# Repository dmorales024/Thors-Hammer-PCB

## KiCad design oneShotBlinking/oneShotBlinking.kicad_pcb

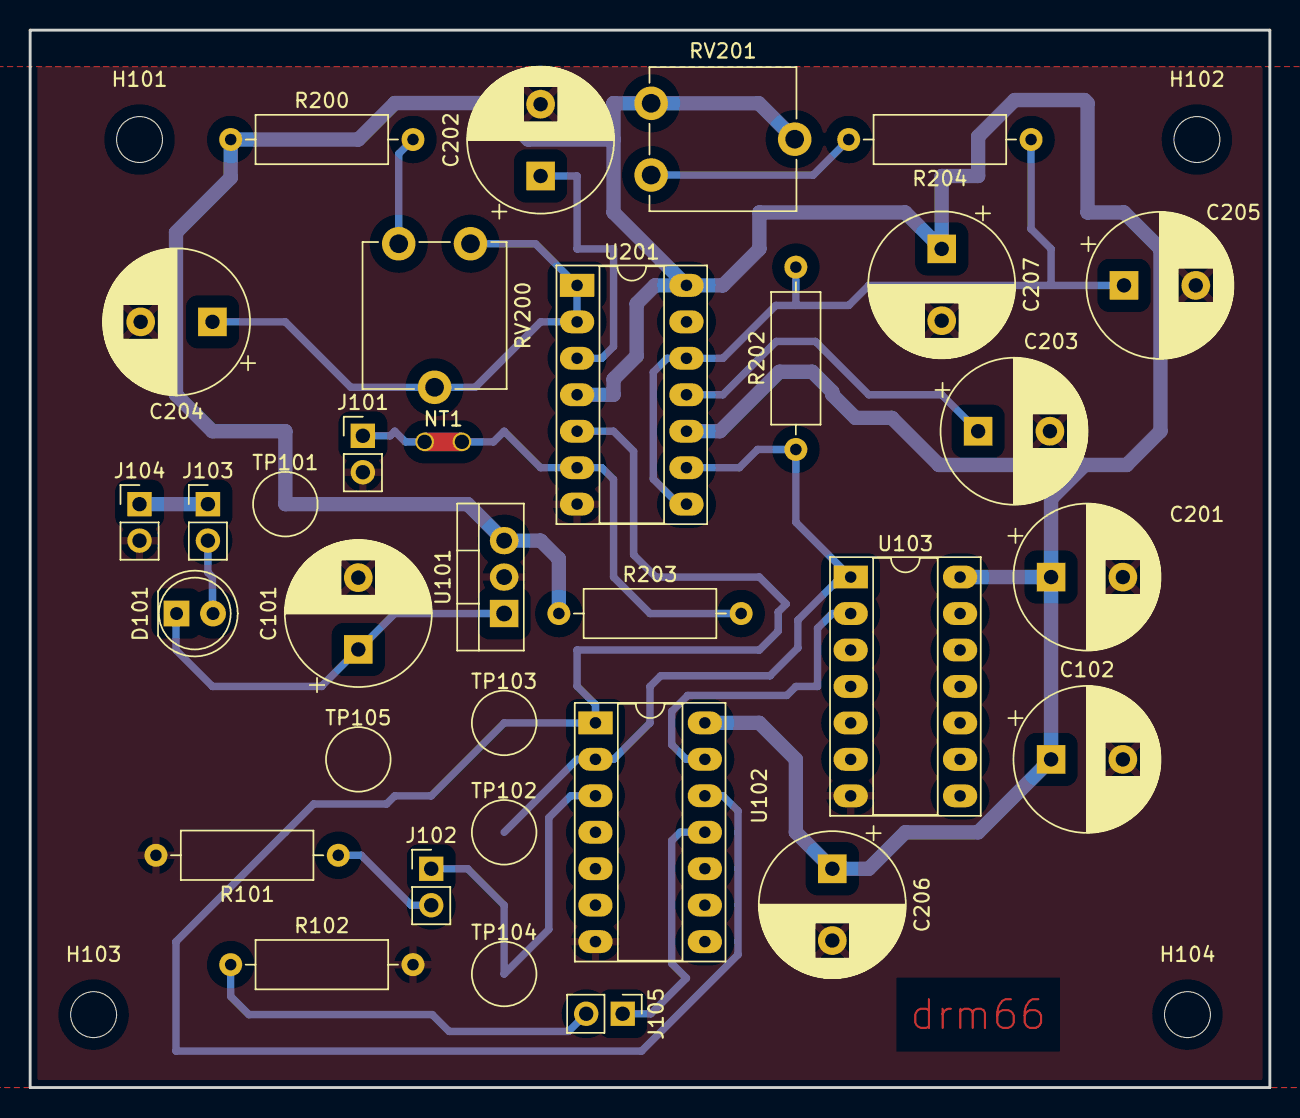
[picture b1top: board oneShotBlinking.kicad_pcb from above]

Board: 2 copper layers, 86.4 x 73.7 mm, 37 parts (0 on the bottom side), 20 nets.

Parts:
C101, C102, C204: 10u; CP_Radial_D10.0mm_P5.00mm
C201, C206, C207: 100n; CP_Radial_D10.0mm_P5.00mm
C202, C203: 0.01u; CP_Radial_D10.0mm_P5.00mm
C205: 1u; CP_Radial_D10.0mm_P5.00mm
D101: RevPol_PwrStatus; LED_D5.0mm
H101, H102, H103, H104: MountingHole; MountingHole_3.2mm_M3
J101: Push Button; PinHeader_1x02_P2.54mm_Vertical
J102, J105: LED; PinHeader_1x02_P2.54mm_Vertical
J103: Power Switch; PinHeader_1x02_P2.54mm_Vertical
J104: BATT; PinHeader_1x02_P2.54mm_Vertical
NT1: To_Button; NetTie-2_THT_Pad1.0mm
R101, R102: 1k; R_Axial_DIN0309_L9.0mm_D3.2mm_P12.70mm_Horizontal
R200: 455k; R_Axial_DIN0309_L9.0mm_D3.2mm_P12.70mm_Horizontal
R202: 42.2k; R_Axial_DIN0309_L9.0mm_D3.2mm_P12.70mm_Horizontal
R203: 10k; R_Axial_DIN0309_L9.0mm_D3.2mm_P12.70mm_Horizontal
R204: 100k; R_Axial_DIN0309_L9.0mm_D3.2mm_P12.70mm_Horizontal
RV200, RV201: 0-100k; Potentiometer_ACP_CA9-V10_Vertical
TP101: VCC; TestPoint_Pad_D4.0mm
TP102: AstableOut; TestPoint_Pad_D4.0mm
TP103: MonoOut; TestPoint_Pad_D4.0mm
TP104: LightOut; TestPoint_Pad_D4.0mm
TP105: GND; TestPoint_Pad_D4.0mm
U101: LM7805_TO220; TO-220-3_Vertical
U102: 4081; DIP-14_W7.62mm_Socket_LongPads
U103: 74LS04; DIP-14_W7.62mm_Socket_LongPads
U201: LM556; DIP-14_W7.62mm_Socket_LongPads

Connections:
+6V: J103.1, J104.1
/Button_Press: J101.1, NT1.1
/Light_Out: J102.1, TP104.1, U102.3
/Light_Out2: J105.1, U102.11
/SW-to-D1: D101.2 (A), J103.2
/Timer/Astable_Output: R202.1, TP102.1, U102.2, U103.1, U201.9 (Q)
/Timer/Astable_Trigger: C205.1, R202.2, R204.1, U201.8 (TR), U201.12 (THR)
/Timer/Monostable_Output: TP103.1, U102.1, U102.12, U201.5 (Q)
/Timer/OneShot_Discharge: C204.1, RV200.2, RV200.3, U201.1 (DIS), U201.2 (THR)
/Timer/OneShot_Trigger: NT1.2, R203.2, U201.6 (TR)
GND: C101.2, C102.2, C201.2, C202.2, C203.2, C204.2, C205.2, C206.2, C207.2, J101.2, J104.2, R101.2, R102.2, TP105.1, U101.2 (GND), U102.7 (VSS), U103.7 (GND), U201.7 (GND)
unnamed: C101.1, D101.1 (K), U101.1 (VI)
unnamed: C202.1, U201.3 (CV)
unnamed: C203.1, U201.11 (CV)
unnamed: J102.2, R101.1
unnamed: J105.2, R102.1
unnamed: R200.2, RV200.1
unnamed: R204.2, RV201.1
unnamed: U102.13, U103.2
VCC: C102.1, C201.1, C206.1, C207.1, R200.1, R203.1, RV201.2, RV201.3, TP101.1, U101.3 (VO), U102.14 (VDD), U103.14 (VCC), U201.4 (R), U201.10 (R), U201.14 (VCC)

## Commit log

2024-05-17 blah
